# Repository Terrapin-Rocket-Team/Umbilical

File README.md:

# Umbilical
software for the umbilical cord

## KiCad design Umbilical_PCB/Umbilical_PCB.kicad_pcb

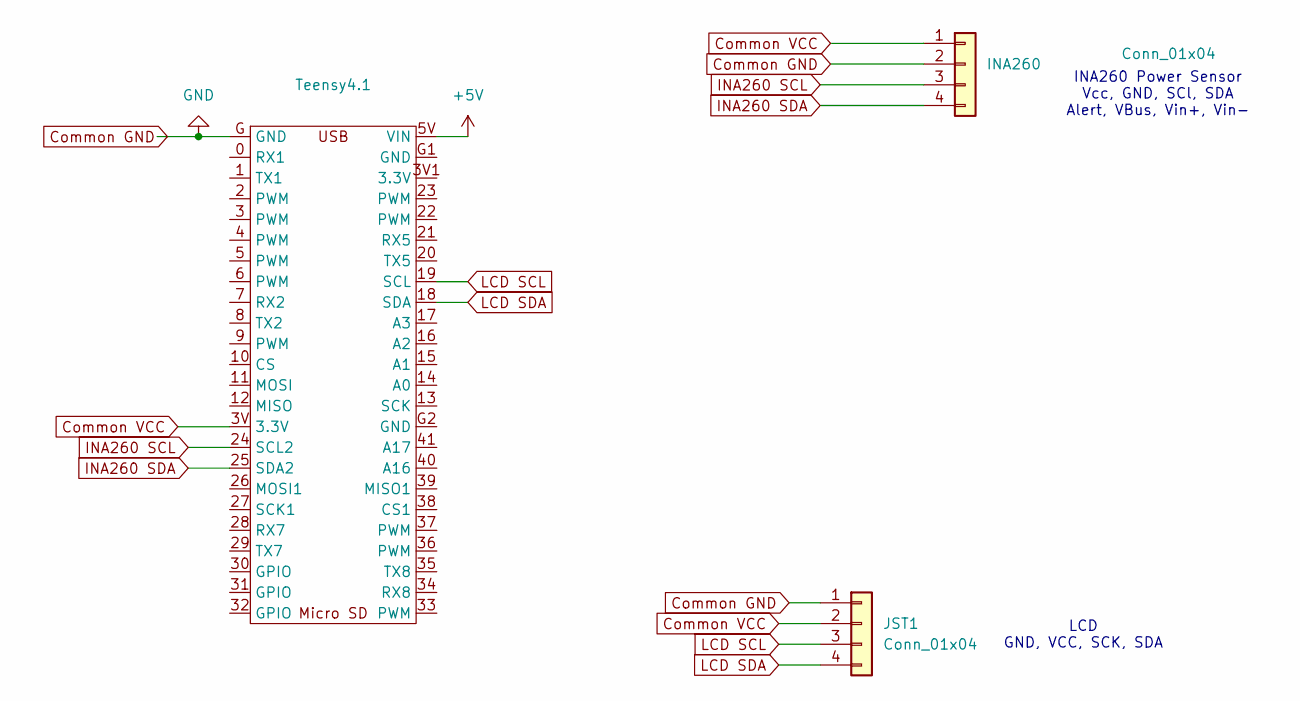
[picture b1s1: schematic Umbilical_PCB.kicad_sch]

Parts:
INA260: Conn_01x04; FanPinHeader_1x04_P2.54mm_Vertical
JST1: Conn_01x04; FanPinHeader_1x04_P2.54mm_Vertical
Teensy4.1: teensy

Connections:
+5V: Teensy4.1.5V (VIN)
Common GND: INA260.2, JST1.1, Teensy4.1.G (GND)
Common VCC: INA260.1, JST1.2, Teensy4.1.3V (3.3V), Teensy4.1.3V1 (3.3V)
INA260 SCL: INA260.3, Teensy4.1.24 (SCL2)
INA260 SDA: INA260.4, Teensy4.1.25 (SDA2)
LCD SCL: JST1.3, Teensy4.1.19 (SCL)
LCD SDA: JST1.4, Teensy4.1.18 (SDA)

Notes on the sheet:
INA260 Power Sensor Vcc, GND, SCl, SDA Alert, VBus, Vin+, Vin-
LCD GND, VCC, SCK, SDA

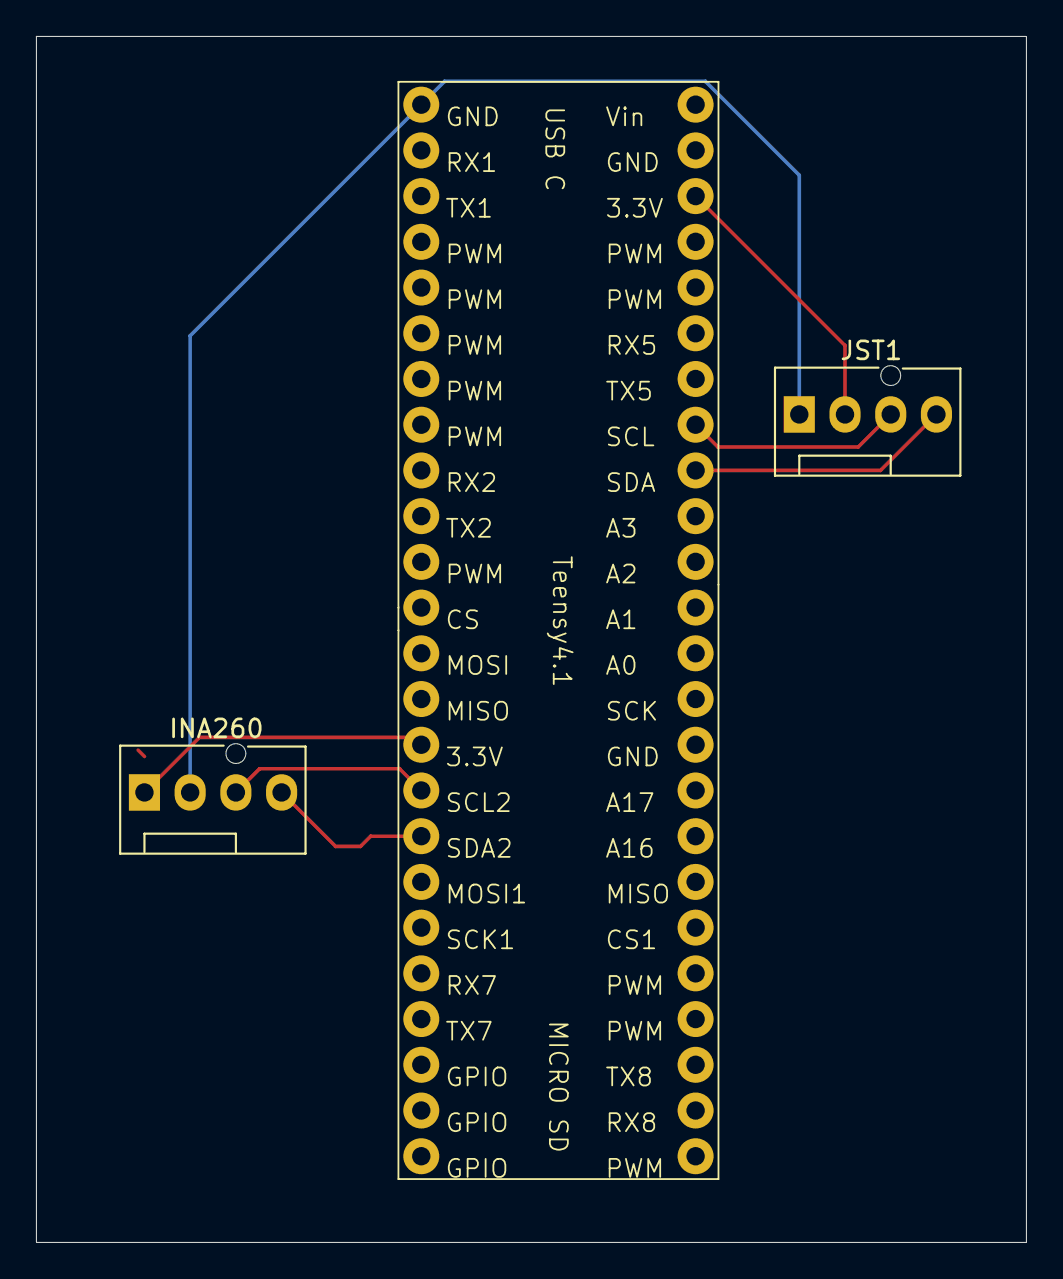
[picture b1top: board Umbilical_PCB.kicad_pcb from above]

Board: 2 copper layers, 55.0 x 67.0 mm, 3 parts (0 on the bottom side), 6 nets.

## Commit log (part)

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2026-05-05 intitial umbilical software, with an initial look over.
